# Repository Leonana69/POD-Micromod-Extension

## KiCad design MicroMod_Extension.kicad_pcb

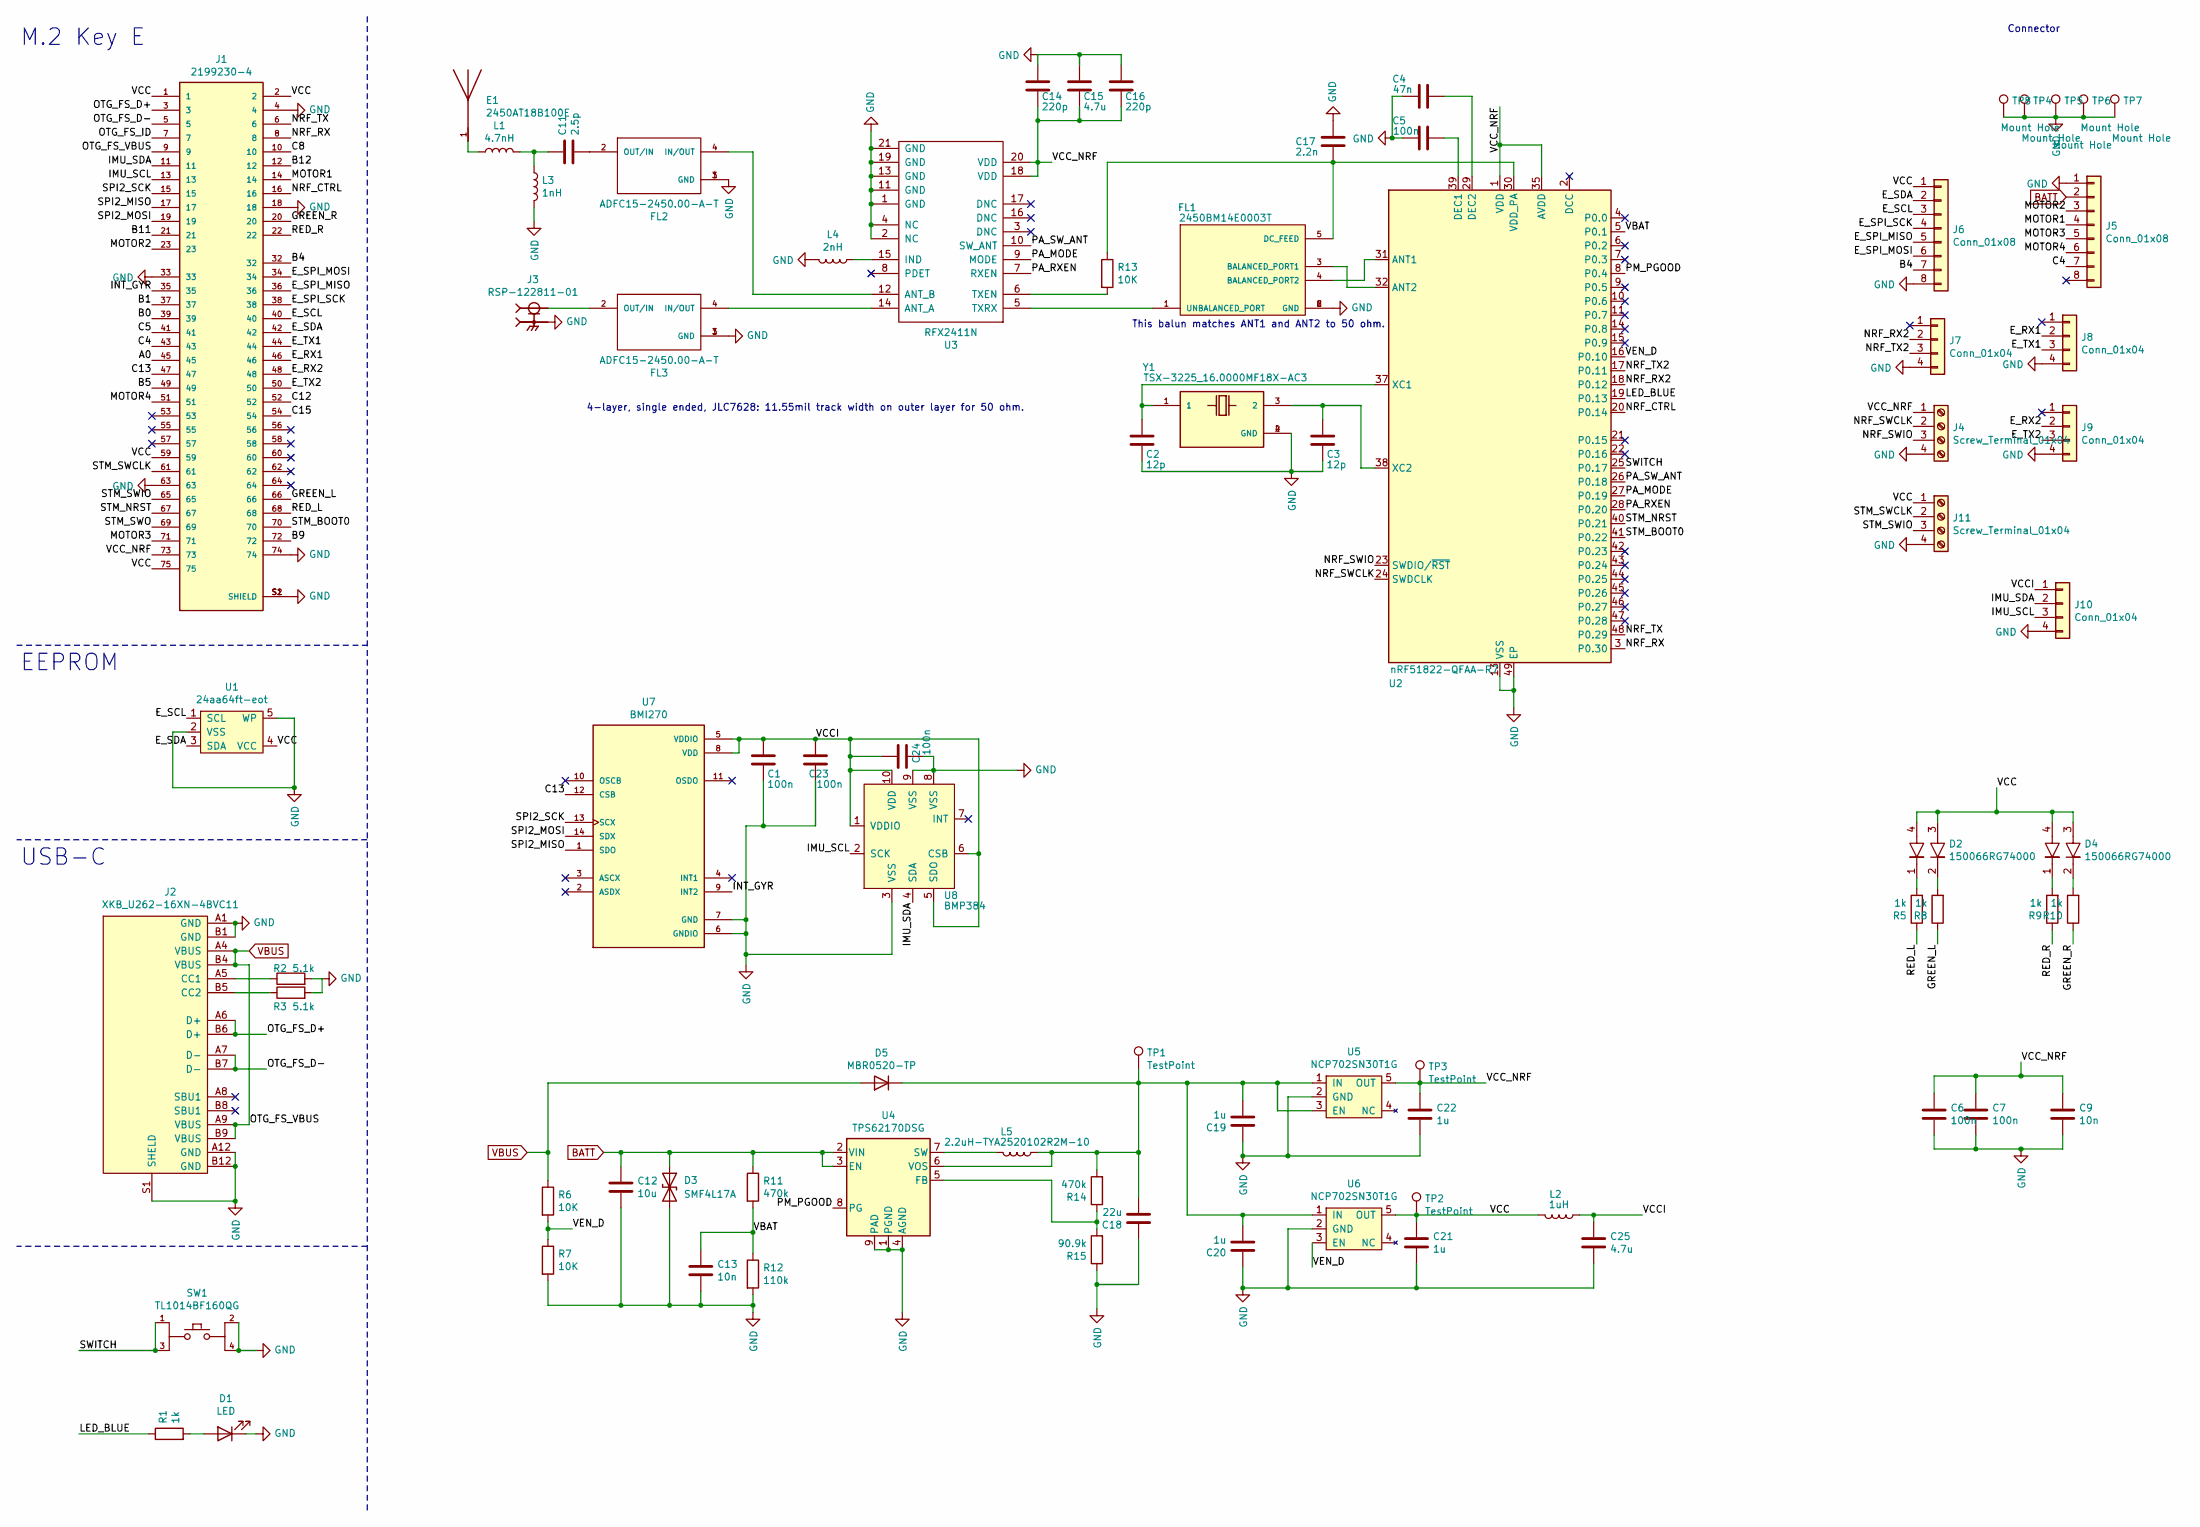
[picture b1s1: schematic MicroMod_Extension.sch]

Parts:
C1, C5, C6, C7, C23, C24: 100n; C_0402_1005Metric
C2, C3: 12p; C_0402_1005Metric
C4: 47n; C_0402_1005Metric
C9, C13: 10n; C_0402_1005Metric
C11: 2.5p; C_0402_1005Metric
C12: 10u; C_0402_1005Metric
C14, C16: 220p; C_0402_1005Metric
C15, C25: 4.7u; C_0402_1005Metric
C17: 2.2n; C_0402_1005Metric
C18: 22u; C_0805_2012Metric
C19, C20, C21, C22: 1u; C_0402_1005Metric
D1: LED; LED-0603
D2, D4: 150066RG74000
D3: SMF4L17A; D_SOD-123
D5: MBR0520-TP; D_SOD-123
E1: 2450AT18B100E; XDCR_2450AT18B100E; PARTREV 4.0
FL1: 2450BM14E0003T; FIL_2450BM14E0003T; PARTREV 3.0
FL2, FL3: ADFC15-2450.00-A-T; FIL_ADFC15-2450.00-A-T; PARTREV 12.03.12
J1: 2199230-4; TE_2199230-4
J2: XKB_U262-16XN-4BVC11; USB_C_Receptacle_XKB_U262-16XN-4BVC11
J3: RSP-122811-01; SAMTEC_RSP-122811-01; PARTREV H
J4, J11: Screw_Terminal_01x04; JST_SUR_SM04B-SURS-TF_1x04-1MP_P0.80mm_Horizontal
J5: Conn_01x08; JST_SH_SM08B-SRSS-TB_1x08-1MP_P1.00mm_Horizontal
J6: Conn_01x08; JST_SUR_BM08B-SURS-TF_1x08-1MP_P0.80mm_Vertical
J7, J8, J9, J10: Conn_01x04; JST_SUR_SM04B-SURS-TF_1x04-1MP_P0.80mm_Horizontal
L1: 4.7nH; L_0402_1005Metric
L2: 1uH; L_0402_1005Metric
L3: 1nH; L_0402_1005Metric
L4: 2nH; L_0402_1005Metric
L5: 2.2uH-TYA2520102R2M-10; L_1008_2520Metric
R1, R5, R8, R9, R10: 1k; R_0402_1005Metric
R2, R3: 5.1k; R_0402_1005Metric
R6, R7, R13: 10K; R_0402_1005Metric
R11, R14: 470k; R_0402_1005Metric
R12: 110k; R_0402_1005Metric
R15: 90.9k; R_0402_1005Metric
SW1: TL1014BF160QG; E-Switch-TL1014BF160QG-0; mouser part number 612-TL1014BF160QG; digikey description SWITCH TACTILE SPST-NO 0.05A 12V
TP1, TP2, TP3: TestPoint; TestPoint_Pad_D1.0mm
TP4, TP5, TP6, TP7: Mount Hole; TestPoint_Plated_Hole_D3.0mm
TP8: Mount Hole; Mounting_Wuerth_WA-SMSI-M2_H2.5mm_9774025243
U1: 24aa64ft-eot; SOT-23-5
U2: nRF51822-QFAA-R7; QFN-48-1EP_6x6mm_P0.4mm_EP4.6x4.6mm
U3: RFX2411N; QFN-20-1EP_3x3mm_P0.4mm_EP1.65x1.65mm
U4: TPS62170DSG; WSON-8-1EP_2x2mm_P0.5mm_EP0.9x1.6mm_ThermalVias
U5, U6: NCP702SN30T1G; TSOT-23-5
U7: BMI270; XDCR_BMI270
U8: BMP384; PQFN45P200X200X100-10N
Y1: TSX-3225_16.0000MF18X-AC3; XTAL_TSX-3225_16.0000MF18X-AC3

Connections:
/A0: J1.45
/B0: J1.39
/B1: J1.37
/B4: J1.32, J6.7
/B5: J1.49
/B9: J1.72
/B11: J1.21
/B12: J1.12
/C4: J1.43, J5.7
/C5: J1.41
/C8: J1.10
/C12: J1.52
/C13: J1.47, U7.12 (CSB)
/C15: J1.54
/E_RX1: J1.46, J8.2
/E_RX2: J1.48, J9.2
/E_SCL: J1.40, J6.3, U1.1 (SCL)
/E_SDA: J1.42, J6.2, U1.3 (SDA)
/E_SPI_MISO: J1.36, J6.5
/E_SPI_MOSI: J1.34, J6.6
/E_SPI_SCK: J1.38, J6.4
/E_TX1: J1.44, J8.3
/E_TX2: J1.50, J9.3
/GREEN_L: J1.66, R8.1
/GREEN_R: J1.20, R10.1
/IMU_SCL: J1.13, J10.3, U8.2 (SCK)
/IMU_SDA: J1.11, J10.2, U8.4 (SDA)
/INT_GYR: J1.35, U7.9 (INT2)
/LED_BLUE: R1.1, U2.19 (P0.13)
/MOTOR1: J1.14, J5.4
/MOTOR2: J1.23, J5.3
/MOTOR3: J1.71, J5.5
/MOTOR4: J1.51, J5.6
/NRF_CTRL: J1.16, U2.20 (P0.14)
/NRF_RX: J1.8, U2.3 (P0.30)
/NRF_RX2: J7.2, U2.18 (P0.12)
/NRF_SWCLK: J4.2, U2.24 (SWDCLK)
/NRF_SWIO: J4.3, U2.23 (SWDIO/~RST)
/NRF_TX: J1.6, U2.48 (P0.29)
/NRF_TX2: J7.3, U2.17 (P0.11)
/OTG_FS_D+: J1.3, J2.A6 (D+), J2.B6 (D+)
/OTG_FS_D-: J1.5, J2.A7 (D-), J2.B7 (D-)
/OTG_FS_ID: J1.7
/PA_MODE: U2.27 (P0.19), U3.9 (MODE)
/PA_RXEN: U2.28 (P0.20), U3.7 (RXEN)
/PA_SW_ANT: U2.26 (P0.18), U3.10 (SW_ANT)
/PM_PGOOD: U2.8 (P0.4), U4.8 (PG)
/RED_L: J1.68, R5.1
/RED_R: J1.22, R9.1
/SPI2_MISO: J1.17, U7.1 (SDO)
/SPI2_MOSI: J1.19, U7.14 (SDX)
/SPI2_SCK: J1.15, U7.13 (SCX)
/STM_BOOT0: J1.70, U2.41 (P0.22)
/STM_NRST: J1.67, U2.40 (P0.21)
/STM_SWCLK: J1.61, J11.2
/STM_SWIO: J1.65, J11.3
/STM_SWO: J1.69
/SWITCH: SW1.1, SW1.3, U2.25 (P0.17)
/VBAT: C13.1, R11.2, R12.1, U2.5 (P0.1)
/VCC: C21.1, D2.3, D2.4, D4.3, D4.4, J1.1, J1.2, J1.59, J1.75, J6.1, J11.1, L2.2, TP2.1, U1.4 (VCC), U6.5 (OUT)
/VCCI: C1.1, C23.2, C24.2, C25.1, J10.1, L2.1, U7.5 (VDDIO), U7.8 (VDD), U8.1 (VDDIO), U8.5 (SDO), U8.6 (CSB), U8.10 (VDD)
/VCC_NRF: C6.1, C7.1, C9.1, C14.2, C15.2, C16.2, C22.1, J1.73, J4.1, TP3.1, U2.1 (VDD), U2.12 (VDD), U2.35 (AVDD), U2.36 (AVDD), U3.18 (VDD), U3.20 (VDD), U5.5 (OUT)
/VEN_D: R6.2, R7.1, U2.16 (P0.10), U6.3 (EN)
BATT: C12.1, D3.1 (A1), J5.2, R11.1, U4.2 (VIN), U4.3 (EN)
GND: C1.2, C2.2, C3.2, C4.1, C5.1, C6.2, C7.2, C9.2, C12.2, C13.2, C14.1, C15.1, C16.1, C17.1, C18.1, C19.1, C20.1, C21.2, C22.2, C23.1, C24.1, C25.2, D1.1 (K), D3.2 (A2), FL1.2 (GND), FL1.6 (GND), FL2.1 (GND), FL2.3 (GND), FL3.1 (GND), FL3.3 (GND), J1.4, J1.18, J1.33, J1.63, J1.74, J1.S1 (SHIELD), J1.S2 (SHIELD), J2.A1 (GND), J2.A12 (GND), J2.B1 (GND), J2.B12 (GND), J2.S1 (SHELD), J3.G1, J3.G2, J4.4, J5.1, J6.8, J7.4, J8.4, J9.4, J10.4, J11.4, L3.2, L4.2, R2.2, R3.2, R7.2, R12.2, R15.1, SW1.2, SW1.4, TP4.1, TP5.1, TP6.1, TP7.1, TP8.1, U1.2 (VSS), U1.5 (WP), U2.13 (VSS), U2.33 (VSS), U2.34 (VSS), U2.49 (EP), U3.1 (GND), U3.2 (NC), U3.4 (NC), U3.11 (GND), U3.13 (GND), U3.19 (GND), U3.21 (GND), U4.1 (PGND), U4.4 (AGND), U4.9 (PAD), U5.2 (GND), U6.2 (GND), U7.6 (GNDIO), U7.7 (GND), U8.3 (VSS), U8.8 (VSS), U8.9 (VSS), Y1.2 (GND), Y1.4 (GND)
unnamed: C2.1, U2.37 (XC1), Y1.1
unnamed: C3.1, U2.38 (XC2), Y1.3 (2)
unnamed: C4.2, U2.29 (DEC2)
unnamed: C5.2, U2.39 (DEC1)
unnamed: C11.1, L1.2, L3.1
unnamed: C11.2, FL2.2 (OUT/IN)
unnamed: C17.2, FL1.5 (DC_FEED), R13.1, U2.30 (VDD_PA)
unnamed: C18.2, C19.2, C20.2, D5.1 (K), L5.1, R14.2, TP1.1, U4.6 (VOS), U5.1 (IN), U5.3 (EN), U6.1 (IN)
unnamed: D1.2 (A), R1.2
unnamed: D2.1, R5.2
unnamed: D2.2, R8.2
unnamed: D4.1, R9.2
unnamed: D4.2, R10.2
unnamed: E1.1, L1.1
unnamed: FL1.1 (UNBALANCED_PORT), U3.5 (TXRX)
unnamed: FL1.3 (BALANCED_PORT1), U2.32 (ANT2)
unnamed: FL1.4 (BALANCED_PORT2), U2.31 (ANT1)
unnamed: FL2.4 (IN/OUT), U3.12 (ANT_B)
unnamed: FL3.2 (OUT/IN), J3.1
unnamed: FL3.4 (IN/OUT), U3.14 (ANT_A)
unnamed: J2.A5 (CC1), R2.1
unnamed: J2.B5 (CC2), R3.1
unnamed: L4.1, U3.15 (IND)
unnamed: L5.2, U4.7 (SW)
unnamed: R13.2, U3.6 (TXEN)
unnamed: R14.1, R15.2, U4.5 (FB)
VBUS: D5.2 (A), J1.9, J2.A4 (VBUS), J2.A9 (VBUS), J2.B4 (VBUS), J2.B9 (VBUS), R6.1

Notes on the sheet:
M.2 Key E
4-layer, single ended, JLC7628: 11.55mil track width on outer layer for 50 ohm.
This balun matches ANT1 and ANT2 to 50 ohm.
EEPROM
USB-C
Connector

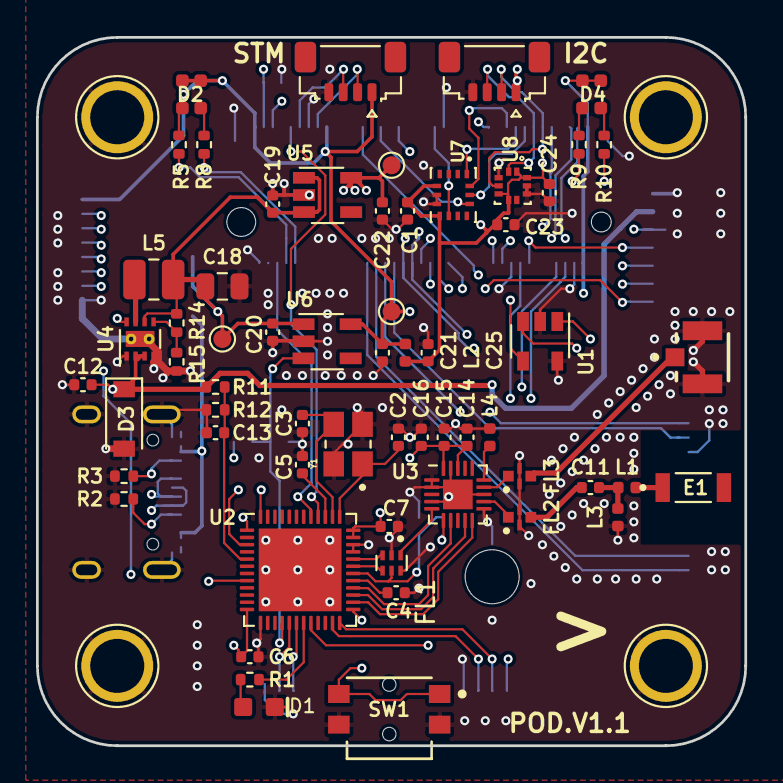
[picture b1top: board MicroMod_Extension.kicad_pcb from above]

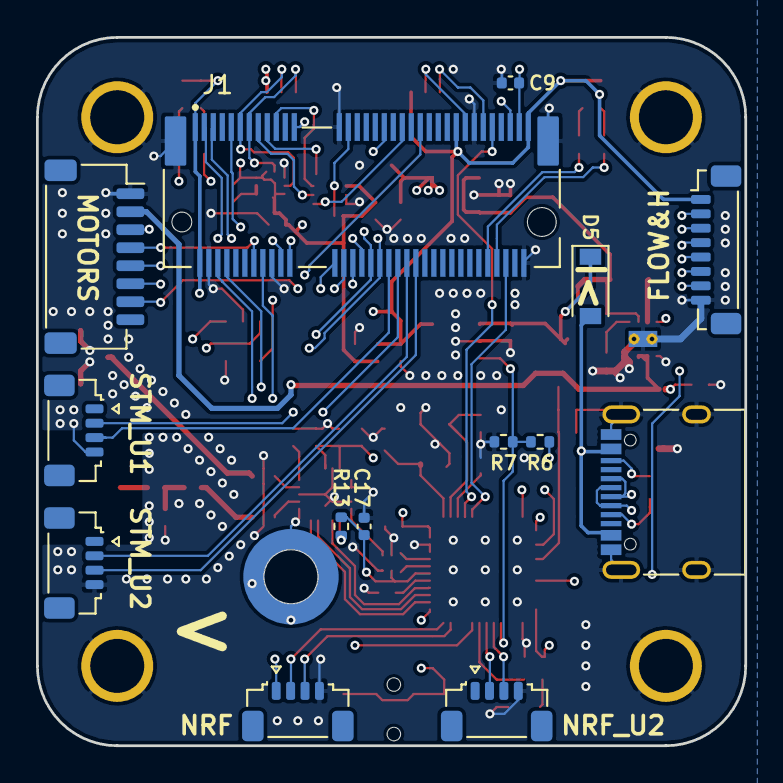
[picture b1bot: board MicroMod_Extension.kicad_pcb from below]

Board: 4 copper layers, 39.4 x 39.4 mm, 80 parts (15 on the bottom side), 79 nets.

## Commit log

2021-10-24 init file
2021-10-25 inductor type
2021-10-26 update RF
2021-10-26 add power management
2021-10-29 add bmi270 and bmp384
2021-10-31 add connector for esc and flow
2021-11-01 update pcb
2021-11-06 finish version 1.0
2021-11-06 submission
2021-11-15 fix bmp384 footprint
2021-11-16 fix screw position
2021-11-17 fix led resistance
2021-11-17 fix switch position
2021-11-19 change motor2 and motor4
2021-11-20 manufacture
2021-11-20 change to iflight esc connection
2022-07-30 add i2c connector
